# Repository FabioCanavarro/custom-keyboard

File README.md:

# Fool's Deck

My custom 65% mechanical keyboard designed from scratch for the Hack Club hardware grant.

| Phase | Date(s) | Time Spent |
| :--- | :---: | ---: |
| Brainstorming & Ideation | July 2 | 1 hr 0 mins |
| Physical Layout (KLE) | July 2 | 1 hr 10 mins |
| PCB Design (KiCad) | July 2 – July 4 | 5 hrs 59 mins |
| 3D Modeling (Onshape) | July 4 – July 5 | 4 hrs 25 mins |
| Total Build Time |  | 12 hrs 34 mins (15 hrs 34 mins, check notes below) |

> Note: Post submit, I realized I sent the wrong bom file so I made the bom file and updated the pcb art, I spent around 3 hours in total? (but I forgot to add photos, so Idk if it can be considered)

> Hours spent is based calculated based on the time difference of each screenshots, as normally I take one when starting and when ending.
> For more specific hours/day tracking, head over to the [Journal dump](journaldump.md) file

## Keyboard Layout

## Keyboard Case

### Top View

### Isometric View

## PCB View

### With PCB Art

### Without PCB Art

## Schematic View

## Specs

- Brain: Raspberry Pi Pico (RP2040)

- Switches: Boba U4T

- Keycaps: Blank White DSA

- Forehead: 0.91" OLED screen + EC11 Rotary Encoder (knob)

## What I built

I made a custom 65% layout with a 5-key macro column on the left (for dev shortcuts) and a "forehead" on the top right for an OLED screen and a knob.

For the case, I went with a 3D-printed tray mount design. It has a bottom tub with 6mm pillars for the PCB to sit on, and a 1.5mm top switch plate that drops right in. I also cut a window in the top plate to expose the Pico and leave room to wire up the OLED.

## Why I built it

I type a lot and wanted a board that actually fits my workflow. But mostly, I just wanted to figure out how hardware actually works. I know how to code, but I had no clue how physical switches turn into keypresses or how to use CAD without the physics engine yelling at me. I wanted to build the whole stack from the circuit board up to the plastic case.

## What I learned

This was a massive learning curve.

- I learned that MX switches need exactly 5mm of gap between the PCB and the switch plate to clip in properly. I almost crushed my Pico because I didn't account for the height of the header pins, which is why I ended up cutting a display window for it in the top plate so it could fit.

- When making the switch plate, I kept accidentally extruding 70 floating cubes instead of a solid plate. I learned how to use projection tools to draw a proper boundary wall around the keys so the software knows what's solid plastic and what's empty space.

- This project has also taught me a lot about Computer Aided Design, specifically in OnShape. 

## Next up

While the PCB and parts are shipping, I'm going to write the firmware in Rust using the RMK framework so I can get the OLED visualizer and knob working.

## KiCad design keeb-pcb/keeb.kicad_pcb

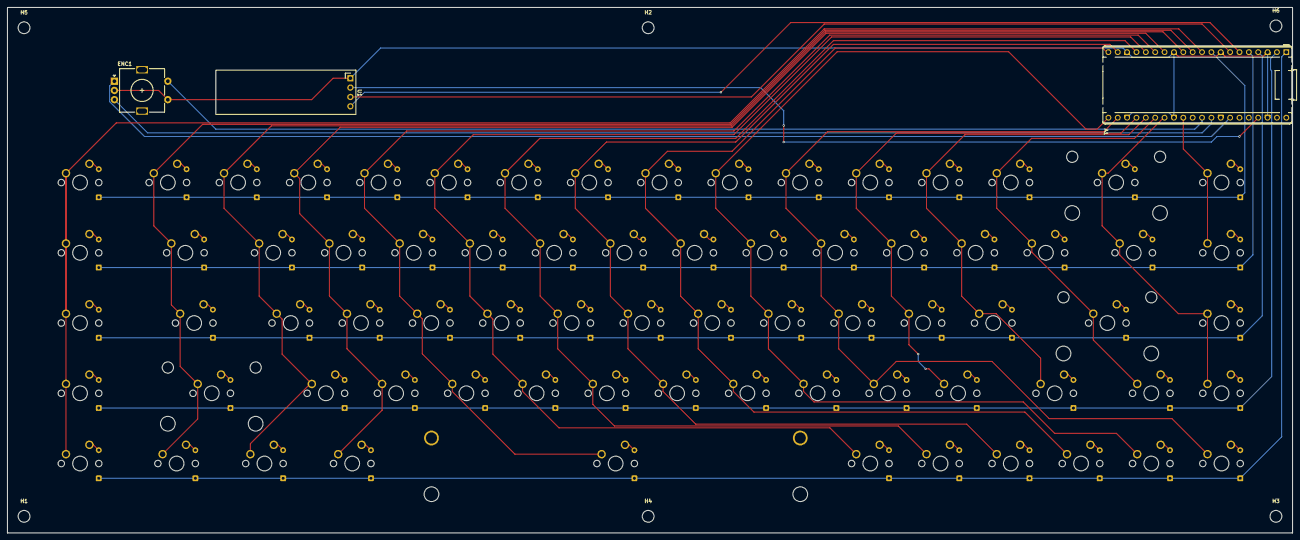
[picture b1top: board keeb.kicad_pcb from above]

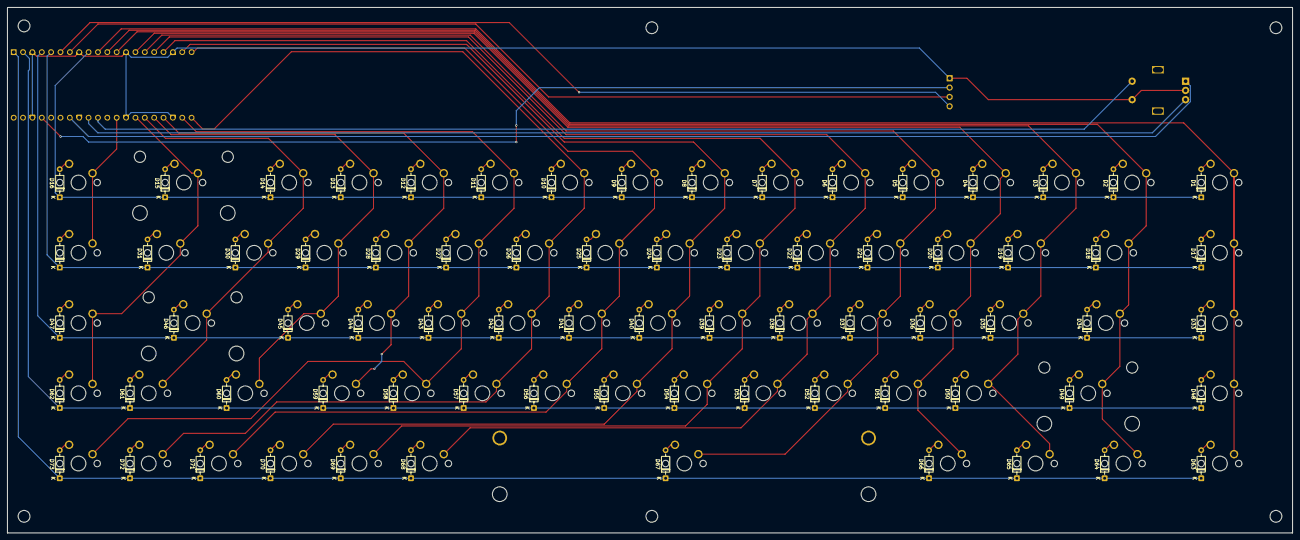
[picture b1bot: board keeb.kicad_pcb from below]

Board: 2 copper layers, 348.5 x 142.5 mm, 159 parts (73 on the bottom side), 101 nets.

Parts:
A1: RaspberryPi_Pico; RaspberryPi_Pico_Common_THT
D1, D2, D3, D4, D5, D6, D7, D8, D9, D10, D11, D12, D13, D14, D15, D16, D17, D18, D19, D20, D21, D22, D23, D24, D25, D26, D27, D28, D29, D30, D31, D32, D33, D34, D35, D36, D37, D38, D39, D40, D41, D42, D43, D44, D45, D46, D47, D48, D49, D50, D51, D52, D53, D54, D55, D56, D57, D58, D59, D60, D61, D62, D63, D64, D65, D66, D67, D68, D69, D70, D71, D72, D73: 1N4148; D_DO-35_SOD27_P7.62mm_Horizontal
ENC1: RotaryEncoder_Switch; RotaryEncoder_Alps_EC11E-Switch_Vertical_H20mm
H1, H2, H3, H4, H5, H6: MountingHole; MountingHole_3.2mm_M3
S1: MX_stab; STAB_MX_2u
S2: MX_stab; STAB_MX_P_6.25u
S3, S4: MX_stab; STAB_MX_2.25u
SW1, SW2, SW3, SW4, SW5, SW6, SW7, SW8, SW9, SW10, SW11, SW12, SW13, SW14, SW15, SW16, SW17, SW18, SW19, SW20, SW21, SW22, SW23, SW24, SW25, SW26, SW27, SW28, SW29, SW30, SW31, SW32, SW33, SW34, SW35, SW36, SW37, SW38, SW39, SW40, SW41, SW42, SW43, SW44, SW45, SW46, SW47, SW48, SW49, SW50, SW51, SW52, SW53, SW54, SW55, SW56, SW57, SW58, SW59, SW60, SW61, SW62, SW63, SW64, SW65, SW66, SW67, SW68, SW69, SW70, SW71, SW72, SW73: SW_Push; SW_MX_1u
U1: ER_OLEDM0.91_1x-I2C

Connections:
/COL0: A1.10 (GPIO7), SW1.1, SW17.1, SW33.1, SW48.1, SW63.1
/COL1: A1.11 (GPIO8), SW2.1, SW18.1, SW34.1, SW49.1, SW64.1
/COL2: A1.12 (GPIO9), SW3.1, SW19.1, SW35.1, SW50.1, SW65.1
/COL3: A1.14 (GPIO10), SW4.1, SW20.1, SW36.1, SW51.1, SW66.1
/COL4: A1.15 (GPIO11), SW5.1, SW21.1, SW37.1, SW52.1, SW67.1
/COL5: A1.16 (GPIO12), SW6.1, SW22.1, SW38.1, SW53.1, SW68.1
/COL6: A1.17 (GPIO13), SW7.1, SW23.1, SW39.1, SW54.1, SW69.1
/COL7: A1.19 (GPIO14), SW8.1, SW24.1, SW40.1, SW55.1, SW70.1
/COL8: A1.20 (GPIO15), SW9.1, SW25.1, SW41.1, SW56.1, SW71.1
/COL9: A1.21 (GPIO16), SW10.1, SW26.1, SW42.1, SW57.1, SW72.1
/COL10: A1.22 (GPIO17), SW11.1, SW27.1, SW43.1, SW58.1, SW73.1
/COL11: A1.24 (GPIO18), SW12.1, SW28.1, SW44.1, SW59.1
/COL12: A1.25 (GPIO19), SW13.1, SW29.1, SW45.1, SW60.1
/COL13: A1.26 (GPIO20), SW14.1, SW30.1, SW46.1, SW61.1
/COL14: A1.27 (GPIO21), SW15.1, SW31.1, SW47.1, SW62.1
/COL15: A1.29 (GPIO22), SW16.1, SW32.1
/ENC_A: A1.34 (GPIO28_ADC2), ENC1.A
/ENC_B: A1.32 (GPIO27_ADC1), ENC1.B
/ROW0: A1.9 (GPIO6), D1.1 (K), D2.1 (K), D3.1 (K), D4.1 (K), D5.1 (K), D6.1 (K), D7.1 (K), D8.1 (K), D9.1 (K), D10.1 (K), D11.1 (K), D12.1 (K), D13.1 (K), D14.1 (K), D15.1 (K), D16.1 (K)
/ROW1: A1.5 (GPIO3), D17.1 (K), D18.1 (K), D19.1 (K), D20.1 (K), D21.1 (K), D22.1 (K), D23.1 (K), D24.1 (K), D25.1 (K), D26.1 (K), D27.1 (K), D28.1 (K), D29.1 (K), D30.1 (K), D31.1 (K), D32.1 (K)
/ROW2: A1.4 (GPIO2), D33.1 (K), D34.1 (K), D35.1 (K), D36.1 (K), D37.1 (K), D38.1 (K), D39.1 (K), D40.1 (K), D41.1 (K), D42.1 (K), D43.1 (K), D44.1 (K), D45.1 (K), D46.1 (K), D47.1 (K)
/ROW3: A1.2 (GPIO1), D48.1 (K), D49.1 (K), D50.1 (K), D51.1 (K), D52.1 (K), D53.1 (K), D54.1 (K), D55.1 (K), D56.1 (K), D57.1 (K), D58.1 (K), D59.1 (K), D60.1 (K), D61.1 (K), D62.1 (K)
/ROW4: A1.1 (GPIO0), D63.1 (K), D64.1 (K), D65.1 (K), D66.1 (K), D67.1 (K), D68.1 (K), D69.1 (K), D70.1 (K), D71.1 (K), D72.1 (K), D73.1 (K)
/gnd: A1.3 (GND), A1.8 (GND), A1.13 (GND), A1.18 (GND), A1.23 (GND), A1.28 (GND), A1.38 (GND), ENC1.C, ENC1.S1, U1.1 (GND)
unnamed: A1.37 (3V3_EN), U1.2 (VCC)
unnamed: A1.6 (GPIO4), U1.4 (SDA)
unnamed: A1.7 (GPIO5), U1.3 (SCL)
unnamed: A1.31 (GPIO26_ADC0), ENC1.S2
unnamed: D1.2 (A), SW1.2
unnamed: D2.2 (A), SW2.2
unnamed: D3.2 (A), SW3.2
unnamed: D4.2 (A), SW4.2
unnamed: D5.2 (A), SW5.2
unnamed: D6.2 (A), SW6.2
unnamed: D7.2 (A), SW7.2
unnamed: D8.2 (A), SW8.2
unnamed: D9.2 (A), SW9.2
unnamed: D10.2 (A), SW10.2
unnamed: D11.2 (A), SW11.2
unnamed: D12.2 (A), SW12.2
unnamed: D13.2 (A), SW13.2
unnamed: D14.2 (A), SW14.2
unnamed: D15.2 (A), SW15.2
unnamed: D16.2 (A), SW16.2
unnamed: D17.2 (A), SW17.2
unnamed: D18.2 (A), SW18.2
unnamed: D19.2 (A), SW19.2
unnamed: D20.2 (A), SW20.2
unnamed: D21.2 (A), SW21.2
unnamed: D22.2 (A), SW22.2
unnamed: D23.2 (A), SW23.2
unnamed: D24.2 (A), SW24.2
unnamed: D25.2 (A), SW25.2
unnamed: D26.2 (A), SW26.2
unnamed: D27.2 (A), SW27.2
unnamed: D28.2 (A), SW28.2
unnamed: D29.2 (A), SW29.2
unnamed: D30.2 (A), SW30.2
unnamed: D31.2 (A), SW31.2
unnamed: D32.2 (A), SW32.2
unnamed: D33.2 (A), SW33.2
unnamed: D34.2 (A), SW34.2
unnamed: D35.2 (A), SW35.2
unnamed: D36.2 (A), SW36.2
unnamed: D37.2 (A), SW37.2
unnamed: D38.2 (A), SW38.2
unnamed: D39.2 (A), SW39.2
unnamed: D40.2 (A), SW40.2
unnamed: D41.2 (A), SW41.2
unnamed: D42.2 (A), SW42.2
unnamed: D43.2 (A), SW43.2
unnamed: D44.2 (A), SW44.2
unnamed: D45.2 (A), SW45.2
unnamed: D46.2 (A), SW46.2
unnamed: D47.2 (A), SW47.2
unnamed: D48.2 (A), SW48.2
unnamed: D49.2 (A), SW49.2
unnamed: D50.2 (A), SW50.2
unnamed: D51.2 (A), SW51.2
unnamed: D52.2 (A), SW52.2
unnamed: D53.2 (A), SW53.2
unnamed: D54.2 (A), SW54.2
unnamed: D55.2 (A), SW55.2
unnamed: D56.2 (A), SW56.2
unnamed: D57.2 (A), SW57.2
unnamed: D58.2 (A), SW58.2
unnamed: D59.2 (A), SW59.2
unnamed: D60.2 (A), SW60.2
unnamed: D61.2 (A), SW61.2
unnamed: D62.2 (A), SW62.2
unnamed: D63.2 (A), SW63.2
unnamed: D64.2 (A), SW64.2
unnamed: D65.2 (A), SW65.2
unnamed: D66.2 (A), SW66.2
unnamed: D67.2 (A), SW67.2
unnamed: D68.2 (A), SW68.2
unnamed: D69.2 (A), SW69.2
unnamed: D70.2 (A), SW70.2
unnamed: D71.2 (A), SW71.2
unnamed: D72.2 (A), SW72.2
unnamed: D73.2 (A), SW73.2

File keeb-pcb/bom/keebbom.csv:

"Id"";""Designator"";""Footprint"";""Quantity"";""Designation"";""Supplier and ref"";
1;""A1"";""RaspberryPi_Pico_Common_THT"";1;""RaspberryPi_Pico"";;;
2;""D1, D2, D3, D4, D5, D6, D7, D8, D9, D10, D11, D12, D13, D14, D15, D16, D17, D18, D19, D20, D21, D22, D23, D24, D25, D26, D27, D28, D29, D30, D31, D32, D33, D34, D35, D36, D37, D38, D39, D40, D41, D42, D43, D44, D45, D46, D47, D48, D49, D50, D51, D52, D53, D54, D55, D56, D57, D58, D59, D60, D61, D62, D63, D64, D65, D66, D67, D68, D69, D70, D71, D72, D73"";""D_DO-35_SOD27_P7.62mm_Horizontal"";73;""1N4148"";;;
3;""ENC1"";""RotaryEncoder_Alps_EC11E-Switch_Vertical_H20mm"";1;""RotaryEncoder_Switch"";;;
4;""S1"";""STAB_MX_2u"";1;""MX_stab"";;;
5;""S2"";""STAB_MX_P_6.25u"";1;""MX_stab"";;;
6;""S3, S4"";""STAB_MX_2.25u"";2;""MX_stab"";;;
7;""SW1, SW2, SW3, SW4, SW5, SW6, SW7, SW8, SW9, SW10, SW11, SW12, SW13, SW14, SW15, SW16, SW17, SW18, SW19, SW20, SW21, SW22, SW23, SW24, SW25, SW26, SW27, SW28, SW29, SW30, SW31, SW32, SW33, SW34, SW35, SW36, SW37, SW38, SW39, SW40, SW41, SW42, SW43, SW44, SW45, SW46, SW47, SW48, SW49, SW50, SW51, SW52, SW53, SW54, SW55, SW56, SW57, SW58, SW59, SW60, SW61, SW62, SW63, SW64, SW65, SW66, SW67, SW68, SW69, SW70, SW71, SW72, SW73"";""SW_MX_1u"";73;""SW_Push"";;;
8;""U1"";""ER_OLEDM0.91_1x-I2C"";1;""ER_OLEDM0.91_1x-I2C"";;;
"
1;"A1";"RaspberryPi_Pico_Common_THT";1;"RaspberryPi_Pico";;;
2;"D1, D2, D3, D4, D5, D6, D7, D8, D9, D10, D11, D12, D13, D14, D15, D16, D17, D18, D19, D20, D21, D22, D23, D24, D25, D26, D27, D28, D29, D30, D31, D32, D33, D34, D35, D36, D37, D38, D39, D40, D41, D42, D43, D44, D45, D46, D47, D48, D49, D50, D51, D52, D53, D54, D55, D56, D57, D58, D59, D60, D61, D62, D63, D64, D65, D66, D67, D68, D69, D70, D71, D72, D73";"D_DO-35_SOD27_P7.62mm_Horizontal";73;"1N4148";;;
3;"ENC1";"RotaryEncoder_Alps_EC11E-Switch_Vertical_H20mm";1;"RotaryEncoder_Switch";;;
4;"S1";"STAB_MX_2u";1;"MX_stab";;;
5;"S2";"STAB_MX_P_6.25u";1;"MX_stab";;;
6;"S3, S4";"STAB_MX_2.25u";2;"MX_stab";;;
7;"SW1, SW2, SW3, SW4, SW5, SW6, SW7, SW8, SW9, SW10, SW11, SW12, SW13, SW14, SW15, SW16, SW17, SW18, SW19, SW20, SW21, SW22, SW23, SW24, SW25, SW26, SW27, SW28, SW29, SW30, SW31, SW32, SW33, SW34, SW35, SW36, SW37, SW38, SW39, SW40, SW41, SW42, SW43, SW44, SW45, SW46, SW47, SW48, SW49, SW50, SW51, SW52, SW53, SW54, SW55, SW56, SW57, SW58, SW59, SW60, SW61, SW62, SW63, SW64, SW65, SW66, SW67, SW68, SW69, SW70, SW71, SW72, SW73";"SW_MX_1u";73;"SW_Push";;;
8;"U1";"ER_OLEDM0.91_1x-I2C";1;"ER_OLEDM0.91_1x-I2C";;;
